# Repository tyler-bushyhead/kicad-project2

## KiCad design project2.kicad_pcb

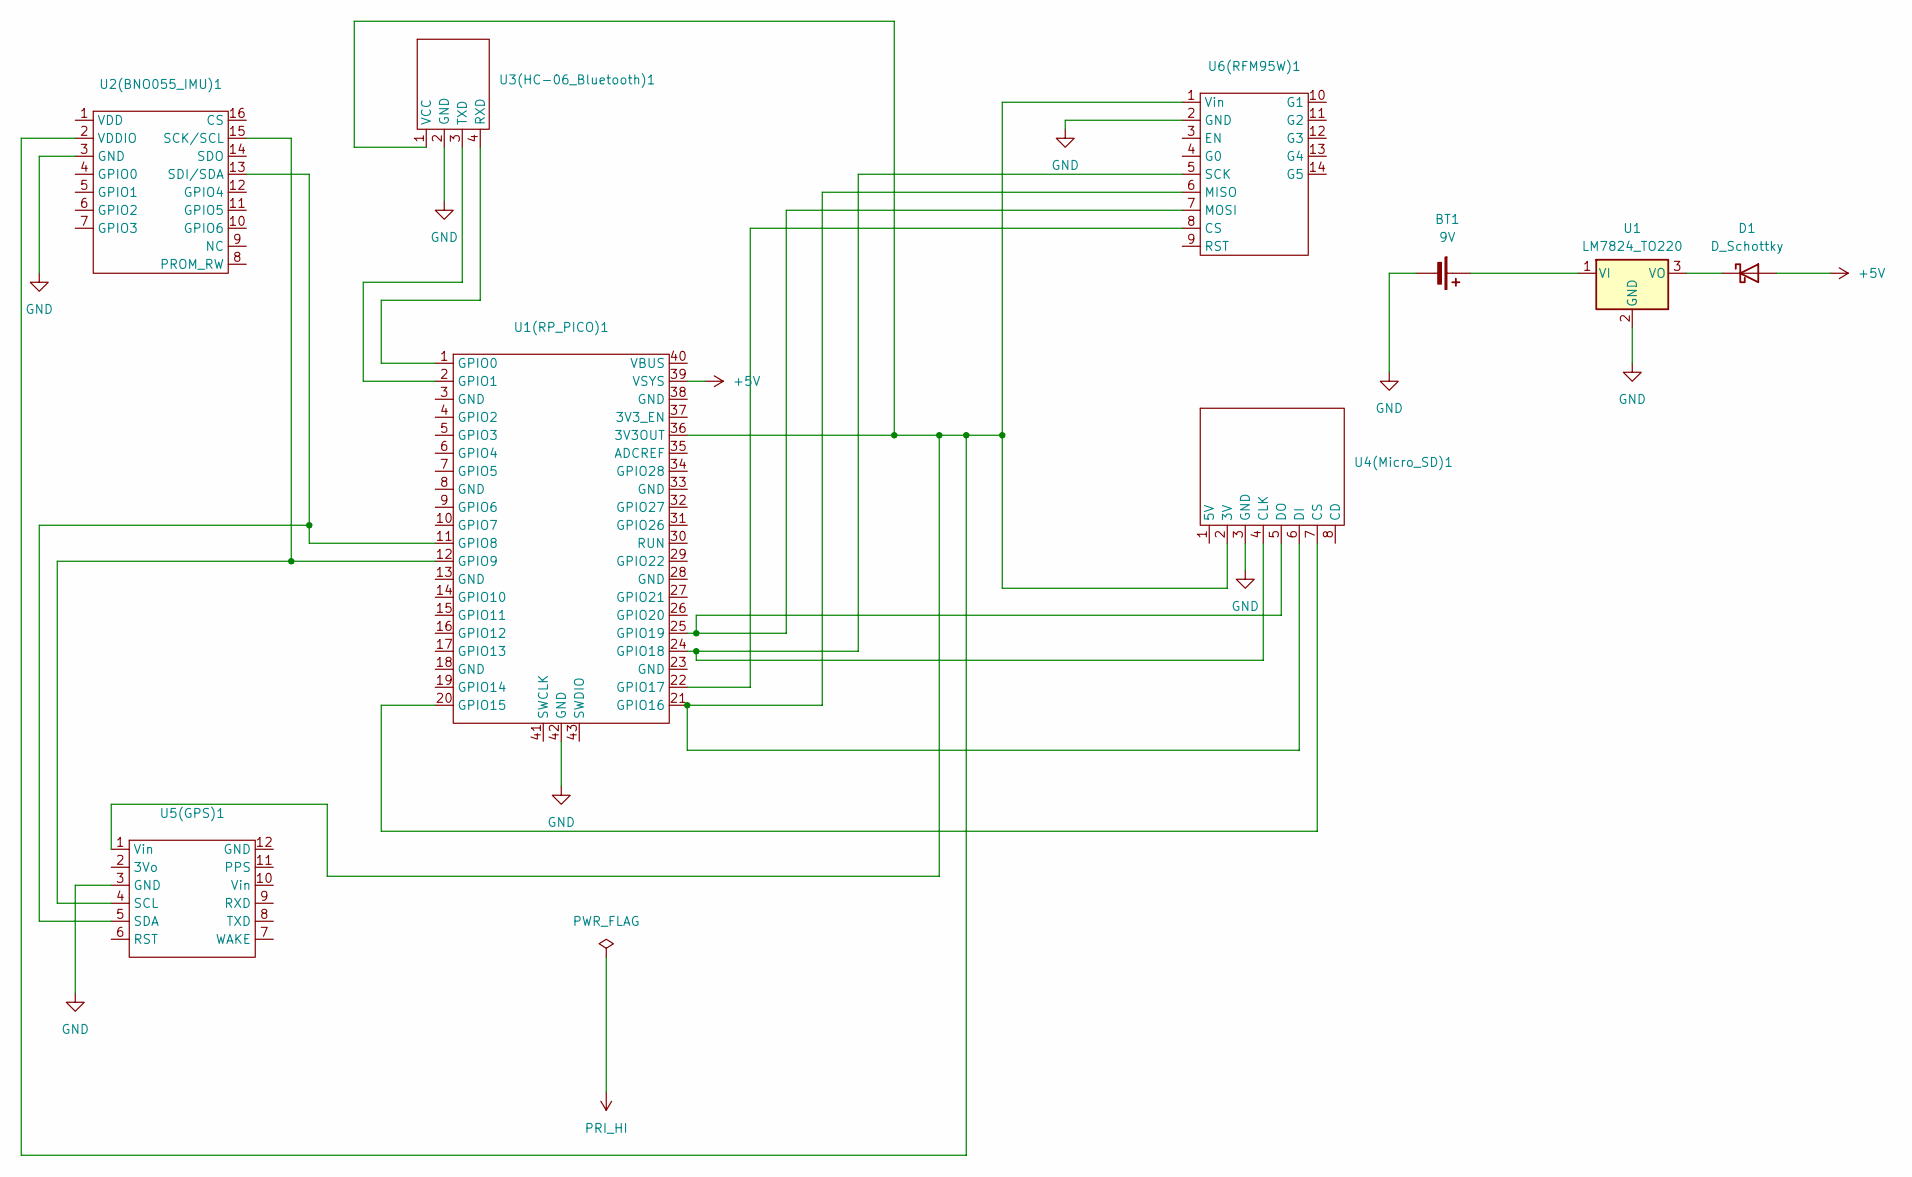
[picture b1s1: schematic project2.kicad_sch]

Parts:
BT1: 9V; BatteryHolder_MPD_BA9VPC_1xPP3
D1: D_Schottky; D_A-405_P2.54mm_Vertical_KathodeUp
U1: LM7824_TO220; TO-220-3_Vertical
U1(RP_PICO)1: RPpico
U2(BNO055_IMU)1: BNO055
U3(HC-06_Bluetooth)1: HC-06
U4(Micro_SD)1: 254SD
U5(GPS)1: PA1010D
U6(RFM95W)1: RFM95W

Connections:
+5V: D1.2 (A), U1(RP_PICO)1.39 (VSYS)
GND: BT1.2 (-), U1.2 (GND), U1(RP_PICO)1.42 (GND), U2(BNO055_IMU)1.3 (GND), U3(HC-06_Bluetooth)1.2 (GND), U4(Micro_SD)1.3 (GND), U5(GPS)1.3 (GND), U6(RFM95W)1.2 (GND)
unnamed: BT1.1 (+), U1.1 (VI)
unnamed: D1.1 (K), U1.3 (VO)
unnamed: U1(RP_PICO)1.36 (3V3OUT), U2(BNO055_IMU)1.2 (VDDIO), U3(HC-06_Bluetooth)1.1 (VCC), U4(Micro_SD)1.2 (3V), U5(GPS)1.1 (Vin), U6(RFM95W)1.1 (Vin)
unnamed: U1(RP_PICO)1.1 (GPIO0), U3(HC-06_Bluetooth)1.4 (RXD)
unnamed: U1(RP_PICO)1.2 (GPIO1), U3(HC-06_Bluetooth)1.3 (TXD)
unnamed: U1(RP_PICO)1.11 (GPIO8), U2(BNO055_IMU)1.13 (SDI/SDA), U5(GPS)1.5 (SDA)
unnamed: U1(RP_PICO)1.12 (GPIO9), U2(BNO055_IMU)1.15 (SCK/SCL), U5(GPS)1.4 (SCL)
unnamed: U1(RP_PICO)1.20 (GPIO15), U4(Micro_SD)1.7 (CS)
unnamed: U1(RP_PICO)1.21 (GPIO16), U4(Micro_SD)1.6 (DI), U6(RFM95W)1.6 (MISO)
unnamed: U1(RP_PICO)1.22 (GPIO17), U6(RFM95W)1.8 (CS)
unnamed: U1(RP_PICO)1.24 (GPIO18), U4(Micro_SD)1.4 (CLK), U6(RFM95W)1.5 (SCK)
unnamed: U1(RP_PICO)1.25 (GPIO19), U4(Micro_SD)1.5 (DO), U6(RFM95W)1.7 (MOSI)

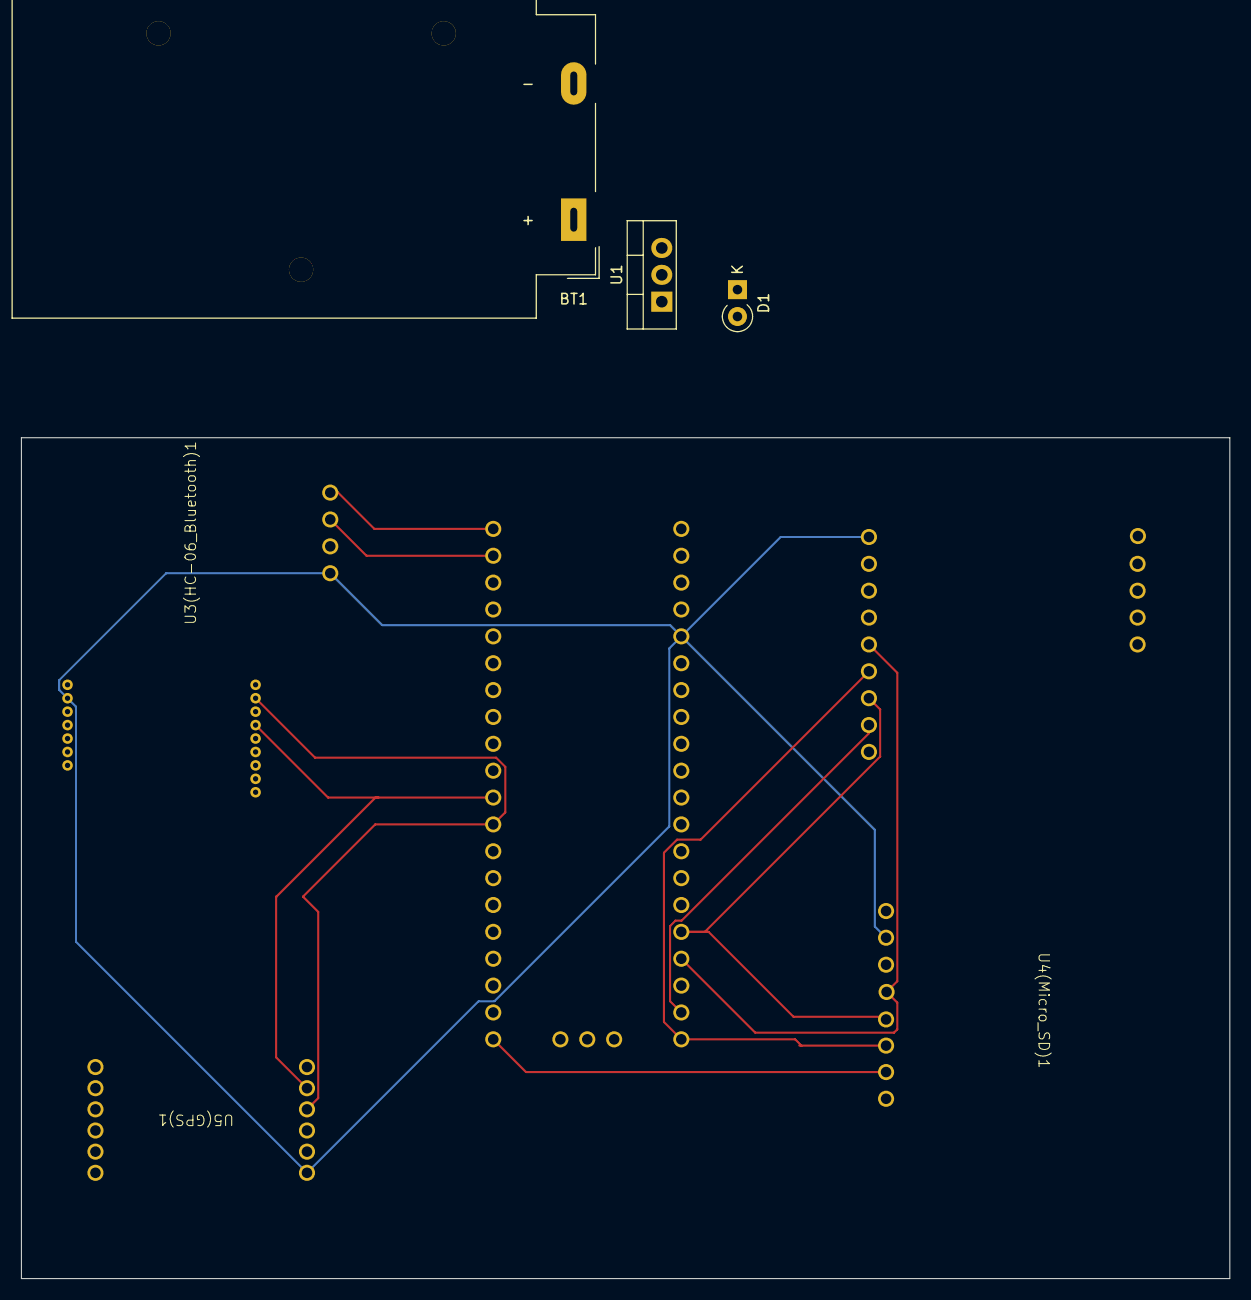
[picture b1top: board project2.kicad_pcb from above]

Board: 2 copper layers, 114.2 x 79.5 mm, 9 parts (0 on the bottom side), 14 nets.
